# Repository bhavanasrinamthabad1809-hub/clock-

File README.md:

## alarm clock 

it is a alarm clock and it has daily morning affirmations and manifestation words so i can read them when i woke up from the  screen and attract the life i always 

## why i made this

from very long time i wanted to integrate the routine of affirmations and manifestation as some of idols mentioned so i feel this is true , i wanted to try it so here i am doing it 

## what it does 
All day: The screen shows the time, today’s date, and one small affirmation, like “I am calm, capable, and ready.”
7:30 AM: The buzzer starts with soft little beeps that slowly get louder. If you want 5 more minutes, tap SW1. To stop it, hold SW1 for 2 seconds.
After you stop it: The screen shows “Good morning,” your affirmation, and your manifestation (“Today I choose calm over worry”). It stays for 30 seconds, then goes back to the clock.
9 PM: Two soft chimes play, and the screen shows an evening affirmation and manifestation, like “You did enough today.” Any button closes it.

## how it works

Time: When you power it on, the ESP32 connects to your WiFi and asks the internet for the exact time. It has no clock battery, so it needs WiFi each time it starts. If WiFi isn’t available, it asks you to set the time by hand.
Alarm: The code checks the time every second. When it matches your alarm time, it starts the buzzer and changes the screen.
Affirmations: The code has lists of sentences. Each day it picks the next one using the date, so the words change daily without any extra work.
Buttons: The four switches control the alarm and screens. SW1 snoozes or stops. SW2 (hold) sets the alarm time, and SW3 and SW4 change the numbers. SW3 on the main screen shows the next affirmation, and SW4 dims the screen for night.

## pcb 

schematic pcb 

pcb routing

## flimware 

arduino ide 

## Bill of Materials

| Component    | Quantity | Description         | Source                       | Price |
| ------------ | -------: | ------------------- | ---------------------------- | ----: |
| ESP32-C3     |        1 | Microcontroller     | [link](https://robu.in/product/seeed-studio-xiao-esp32c3-tiny-mcu-board-with-wi-fi-and-ble-battery-charge-supported-power-efficiency-and-rich-interface/) | 749  |
| tft Display |        1 | Small display       | [link](https://robu.in/product/2-4-inch-spi-interface-240x320-touch-screen-tft-display-module/) |700 |
| switches  |        3 | User input buttons  | [link](https://amzn.in/d/0aKbDkSN) | 359 |
| PCB          |        1 | Custom-designed PCB | [link](https://jlcpcb.com/)  | 375 |
| buzzer | 1 | alarm sound | [Link](https://robu.in/product/1-month-warranty-1248/) | 151 |

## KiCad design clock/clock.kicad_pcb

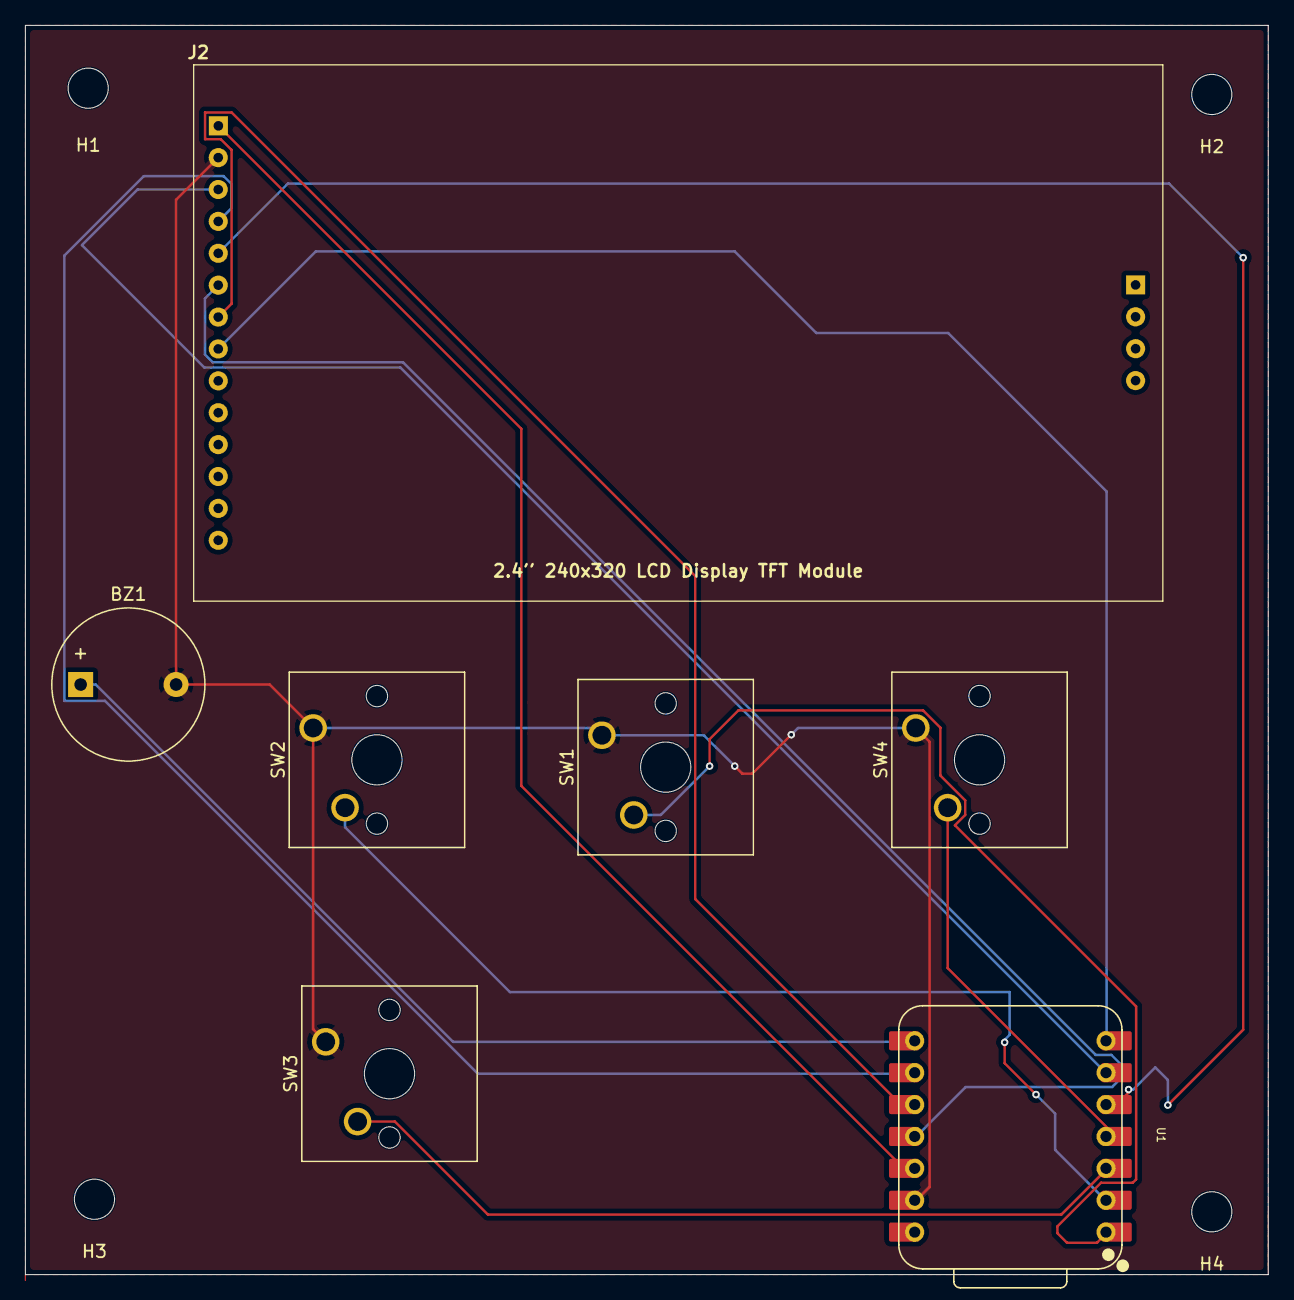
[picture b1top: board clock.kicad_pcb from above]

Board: 2 copper layers, 99.0 x 99.5 mm, 11 parts (0 on the bottom side), 13 nets.

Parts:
BZ1: Buzzer; Buzzer_12x9.5RM7.6
H1, H3: MountingHole; MountingHole_3.2mm_M3
H2: Hole; MountingHole_3.2mm_M3
H4: hole; MountingHole_3.2mm_M3
J2: Conn_01x14_Pin; 2.4_240x320_LCD_Display_TFT_Module
SW1, SW2, SW3, SW4: SW_Push; SW_Cherry_MX_1.00u_PCB
U1: XIAO-ESP32-C3-SMD; XIAO-ESP32-C6-DIP

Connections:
+3.3V: J2.1, U1.12 (3V3_OUT)
/bl: J2.8, U1.7 (D6)
/cs: J2.3, U1.6 (D5)
/dc: J2.5, U1.5 (D4)
/mosi: J2.6, U1.11 (D10)
/rst: J2.4, U1.9 (D8)
/sck: J2.7, U1.10 (D9/BOOT)
GND: BZ1.2 (-), J2.2, SW1.1, SW2.1, SW3.1, SW4.1, U1.13 (GND)
unnamed: BZ1.1 (+), U1.8 (D7)
unnamed: SW1.2, U1.1 (D0)
unnamed: SW2.2, U1.2 (D1)
unnamed: SW3.2, U1.3 (D2)
unnamed: SW4.2, U1.4 (D3)
